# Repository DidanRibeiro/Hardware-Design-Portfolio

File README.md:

# Hardware-Design-Portfolio
Neste repositório compartilho todos meus trabalhos de Hardware utilizando ferramentas CAD de captura de circuitos como Proteus, Eagle e Altium Design de maneira aberta, porém sem fins comerciais para quem deseja utilizar para prover adaptações em seus projetos.

In this repository I share all my hardware work using CAD capture tools such as Proteus, Eagle and Altium Design in an open but non-commercial way for those who want to use to provide adaptations in their projects.

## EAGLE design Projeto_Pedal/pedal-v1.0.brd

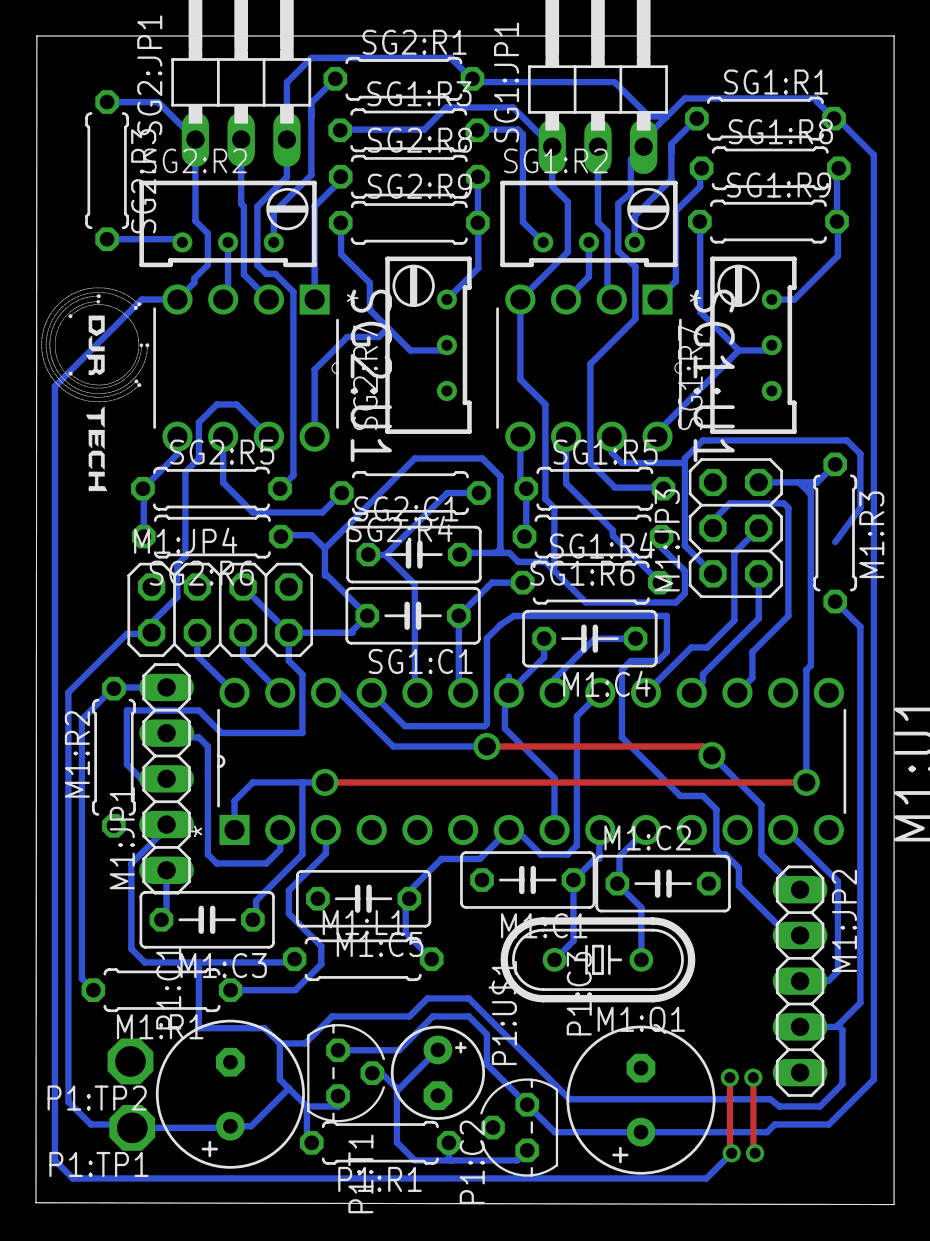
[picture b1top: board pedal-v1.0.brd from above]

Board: 2 copper layers, 47.7 x 64.9 mm, 48 parts (0 on the bottom side), 41 nets.

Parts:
M1:C1, M1:C2: 22p; C050-030X075
M1:C3: C050-030X075
M1:C4, M1:C5: 100n; C050-030X075
M1:JP1, M1:JP2: 1X05
M1:JP3: 2X03
M1:JP4: 2X04
M1:L1: 10m; 0207/7
M1:Q1: HC49/S
M1:R1: 22k; 0207/7
M1:R2: 33k; 0207/7
M1:R3: 10K; 0207/7
M1:U1: ATMEGA328P-PU; DIP254P762X457-28
P1:C1, P1:C3: 100u; E3,5-8
P1:C2: 10u; E2,5-5
P1:R1: 390; 0207/7
P1:T1: bc548; TO92
P1:TP1, P1:TP2: TPPAD1-17; P1-17
P1:U$1: TL431LP; TO92
SG1:C1, SG2:C1: 220n; C050-030X075
SG1:JP1, SG2:JP1: 1X03/90
SG1:R1, SG1:R3, SG2:R1, SG2:R3: 47k; 0207/7
SG1:R2, SG2:R2: 1k; RTRIM64W
SG1:R4, SG2:R4: 68k; 0207/7
SG1:R5, SG1:R6, SG2:R5, SG2:R6: 10k; 0207/7
SG1:R7, SG2:R7: RTRIM64W
SG1:R8, SG2:R8: 33; 0207/7
SG1:R9, SG2:R9: 0; 0207/7
SG1:U1, SG2:U1: INA122P; DIP254P762X508-8
U$1: LOGO

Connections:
2V5: P1:C3.+, P1:T1.3, P1:U$1.1, SG1:JP1.3, SG1:R1.2, SG1:R5.2, SG2:JP1.3, SG2:R1.2, SG2:R5.2
+5V: M1:JP1.2, M1:JP2.4, M1:JP3.2, M1:JP4.1, M1:L1.1, M1:R3.2, P1:C1.+, P1:R1.2, P1:T1.1, P1:TP1.TP, SG1:U1.7, SG2:U1.7
GND: M1:C1.2, M1:C2.2, M1:C4.2, M1:C5.2, M1:JP1.3, M1:JP2.5, M1:JP3.6, M1:JP4.6, M1:JP4.7, M1:R2.1, M1:U1.8, M1:U1.22, P1:C1.-, P1:C2.-, P1:C3.-, P1:TP2.TP, P1:U$1.2, SG1:C1.2, SG1:JP1.1, SG1:R3.1, SG1:R6.1, SG1:U1.4, SG2:C1.2, SG2:JP1.1, SG2:R3.1, SG2:R6.1, SG2:U1.4
M1:2V5: M1:C4.1, M1:U1.21
M1:!RESET: M1:C3.1, M1:JP3.5, M1:R3.1, M1:U1.1
M1:MISO: M1:JP3.1, M1:U1.18
M1:MOSI: M1:JP3.4, M1:U1.17
M1:N$1: M1:JP1.5, M1:R1.2, M1:R2.2
M1:N$2: M1:JP1.4, M1:U1.2
M1:N$3: M1:C1.1, M1:Q1.2, M1:U1.9
M1:N$4: M1:C2.1, M1:Q1.1, M1:U1.10
M1:N$5: M1:R1.1, M1:U1.3
M1:N$6: M1:C3.2, M1:JP1.1
M1:N$7: M1:C5.1, M1:L1.2, M1:U1.7, M1:U1.20
M1:PC2: M1:JP2.2, M1:U1.25
M1:PC3: M1:JP2.1, M1:U1.26
M1:PD7: M1:JP2.3, M1:U1.13
M1:SCK: M1:JP3.3, M1:U1.19
M1:SCL: M1:JP4.3, M1:U1.28
M1:SDA: M1:JP4.5, M1:U1.27
unnamed: M1:U1.23, SG1:C1.1, SG1:R4.1
unnamed: M1:U1.24, SG2:C1.1, SG2:R4.1
P1:N$1: P1:C2.+, P1:R1.1, P1:T1.2, P1:U$1.3
SG1:IN-: SG1:JP1.2, SG1:U1.2
SG1:N$1: SG1:R1.1, SG1:R2.3
SG1:N$2: SG1:R2.1, SG1:R3.2
SG1:N$3: SG1:R4.2, SG1:U1.6
SG1:N$5: SG1:R2.2, SG1:U1.3
SG1:N$6: SG1:R5.1, SG1:R6.2, SG1:U1.5
SG1:N$7: SG1:R8.1, SG1:U1.1
SG1:N$8: SG1:R7.3, SG1:R8.2, SG1:R9.2
SG1:N$9: SG1:R7.2, SG1:R9.1, SG1:U1.8
SG2:IN-: SG2:JP1.2, SG2:U1.2
SG2:N$1: SG2:R1.1, SG2:R2.3
SG2:N$2: SG2:R2.1, SG2:R3.2
SG2:N$3: SG2:R4.2, SG2:U1.6
SG2:N$5: SG2:R2.2, SG2:U1.3
SG2:N$6: SG2:R5.1, SG2:R6.2, SG2:U1.5
SG2:N$7: SG2:R8.1, SG2:U1.1
SG2:N$8: SG2:R7.3, SG2:R8.2, SG2:R9.2
SG2:N$9: SG2:R7.2, SG2:R9.1, SG2:U1.8

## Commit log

2019-04-20 Projeto Vale de 2017 adicionado com todos os arquivos de esquemático, layout e relatório. Foi utilizado o software Proteus.
2019-04-20 Added Design files for Switching Power Supply project, 6 layers layout
2019-04-20 Added Contador Geiger project with all files design. Thats a personal project which was born from Modern Physics subject I took during my undergraduation at UnB
2019-04-20 Projeto Pedal added with all design file from Eagle PCB
2019-04-20 Added my first commercial project that I made using proteus on year 2016
2019-04-20 Added project files that I design for customers, without any details about how it works
2019-04-20 Added design files for Automation System shield for Esp32 usin Altium Design
2022-04-04 Add files via upload
    Um breve resumo de meu portfolio desde projetos pessoais a empresas que me deram um voto de confiança e a oportunidade de desenvolver minhas habilidades e meu trabalho como engenheiro de hardware.
